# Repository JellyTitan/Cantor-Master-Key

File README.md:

# Cantor Master Key (Formerly 'Cantor MX')
This is a Cantor variant adjusted to support multiple switches, add hot swop kailh V1 & V2 sockets, and add a speaker.
> [!ALERT]
> ALL WORK HAS STOPPED ON THIS REPO. After multiple iterations, I concluded that this is a poor idea and abbandonded the project. The pins on the footprints are all just a little different, so it comes out looking like swiss cheese, and really not working well at all. Ultimately i found that  without three solid points of contact, the switches would be 'jiggly'. The jiggle would require keyplates, and the keyplates added cost & complexity. Reducing cost and complexity was driving this project. 

Version 1.4 **(UNTESTED)** adds:
* breakoff pinky clusters
* Keys 4, 14 & 25 fixed ground zone islands
* Updated switch footprint to prevent ground islands.
* Fixed Choc slot off center by .1 to fix slight skew. (Updated wrapping solder mask.)
* Combined cherry mx and red dragon hole to reduce drilling. 
* Fixed broken speaker footprint.
* ~~todo: Poke-yoke ground zone errors by connecting all gnd pads in footrpint~~

Version 1.3 **(TESTED - Buggy)** (PCB ~~ordered~~ received) currently supports:
* **NOTE TO SELF: In v1.3 Keys 4, 14 & 25 have ground zone islands - these switches will probably not work!!**
* Cherry MX full size 5 pin only. (Aka "[PCB mount](https://deskthority.net/wiki/Switch_mount)")
* [Cherry MX Low profile](https://www.cherrymx.de/en/cherry-mx/mx-low-profile/mx-low-profile-red.html) (Aka "MXLP") 
* [Gateron Low Profile](https://www.gateron.co/products/gateron-low-profile-mechanical-switch-set) (KS-27)
* [Kailh Choc V1](http://www.kailh.com/en/Products/Ks/CS/321.html) (PG1350) - Can use hotswap sockets or be soldered in.
* [Kailh Choc V2](http://www.kailh.com/en/Products/Ks/CS/757.html) (PG1353) - Can use hotswap sockets or be soldered in.
* [TTC KS32](https://deskthority.net/wiki/TTC_KS32_series) (Cherry MX Low Profile Clones)
* RedDragon MX Low profile (No data sheet available - these probably don't work?) 

This version _does not_ support
* Cherry MX full size 3 pin, aka "[Plate mount](https://deskthority.net/wiki/Switch_mount)". (Only 2 good points of contact, so it's too wiggly. Would need a plate).
* [Kailh Notebook "X" Scissor](http://www.kailh.com/en/Products/Ks/NotebookS/649.html) (CPG142501D02) The corner mounting holes conflict with Kailh V2 corner pin. That pin is not electrically relevent, but helps with orientation. Maybe add this in the future?
* Cherry MX [Ultra low profile](https://www.cherrymx.de/en/cherry-mx/mx-ultra-low-profile/mx-ulp-click.html) (Too hard to find).

All of these except the Choc V1s will use MX keycaps. MX keycaps are slightly larger than Choc V1 caps that are used in the original cantor so the layout has been adjusted accordingly. None of the routing has changed, so any Cantor V1.0 firmware will work with the board.

* V1.1 (pcb/gerbers/Cantor_MXv1.1.zip) has been produced with JLCPCB and confirmed to work. This only supports choc v1, choc v2, and MX full size switches. When using full size cherry MX switches, the 5 pin is recommended because the center hole is enlarged to support Kailh Chocs, so the 3 pin full size cherry MX switch will be unstable. It's still workable, but you'll likely have a few tilted keys, or need to create a plate.
* V1.3 Is a work in progress and has not been validated. This version has additonal key support. I threw in a piezo speaker too because, why not?
Improved pin hole dimensions for 3 pin cherry MX stability. Moved TRRS jack to allow for larger thumb cluster keycaps.

Todo:
* Updated the licensing?
* Update schematic for TX/RX TRRS Crossover.
* ~~Should this be updated for the pi2040 (Currently uses blackpill 401).~~ There is already a "Piantor". If this footprint works, make a mash up. 
* On test print 1.3, red was extra, so i went with blue. Try Elecrow next time?
* On test print 1.3, 4-6-23, jlcpcb charged an extra $7.50USD for having an abundance of slots. Try elecrow, or reduce slots. Maybe make the blackpill flippable to reduce by 40 apertures? (Pulling red dragon only reduces by 21 slots, since it shares a ground).

V1.4

V1.3

V1.1

## How to order this board from a PCB vendor.

Helpful info if it's your first time ordering a PCB.

Most PCB vendors have a similar ordering process. I use [JLCPCB](https://jlcpcb.com/) because they are usually the most cost effective. I've had good luck with [Elecrow](https://www.elecrow.com/) too. [You can find PCB price comparison tools online.](https://pcbshopper.com/) When comparing pricing, the board dimensions are 99 x 143mm. (Usually anything under 100x100mm is really cheap - so be sure to use those dimensions when pricing).

The production files are known as "gerbers", and they are usually uploaded as a `.zip` file. (It's essentially a collection of files for each layer of the board, like holes, graphics, traces etc.) In this repo, the file is at `cantor-choc-V2/pcb/Gerbers_ChocV2/Cantor_Choc_V2.zip`. (File & path name may change during development)

@todo - revise path before pull request.

The homepage of JLCPCB has a drag & drop upload. Drag the gerber `.zip` and drop it on the "add gerber file" box.

While the file is uploading, it will take you to an options screen. Once the board size is detected<sup>1</sup>, the price<sup>3</sup> will update accordingly.
Changing the pcb color<sup>2</sup> may impact production time and price.
Shipping estimates<sup>4</sup> can vary widely, so be sure to check those. (You'll see these options again during checkout).

It's worth noting, the default pcb surface finish contains Lead. For boards in cases, this is usually not a problem. If you're going to rock a naked board, consider going with "lead free" for a few bucks more.

`@todo - Site sources?`

The remainder of the checkout process is standard ecommerce stuff. After you pay for your order, it will be reviewed before going into production. They will let you know if the file has any issues.

# Cantor Keyboard
The Cantor keyboard is a 42 key diodeless split keyboard, designed with simplicity in mind. It is inspired on the popular [corne](https://github.com/foostan/crkbd), [ferris](https://github.com/pierrechevalier83/ferris) and [sweep](https://github.com/davidphilipbarr/Sweep) keyboards, aiming to provide a more ergonomic (stronger column stagger) corne-like layout with a simple, easy to assemble and cheap design.

The keyboard uses choc switches with choc spacing. Therefore, only MBK keycaps can be used.

### Why diodeless?

A diodeless design reduces the keyboard assembly time, as the amount of components to solder is significantly reduced.
Moreover, soldering diodes can cause trouble during the keyboard build. Diodes need to be placed in the correct direction, if not, the keys won't work well!
Eliminating diodes will prevent many errors during the assembly process.

## Disclaimers

All the designs and files are provided "AS IS" without any warranty or support.

## Design philosophy

The Cantor is designed with the following goals:

- Comfort
- Powerful
- Low cost
- Simplicity
- Ease of build
- USB-C
- No diodes

The PCB is reversible to reduce manufacturing costs.

## Getting started

Would you like to build this keyboard? Then continue reading!

You can also buy a kit to build the Cantor keyboard from one of the **honorable sponsors**:

<br><br><br><br>

### Bill of Materials

To build the keyboard, you will need the following materials:

- 2x PCB boards (both are equal since they are reversible)
- 2x STM32F401CC blackpill microcontrollers (they are cheap on aliexpress)
- Pins and sockets for the microcontrollers (blackpill needs 20 pin stripes)
- 42 Choc v1 switches
- 42 MBK keycaps
- Some little rubber feet/bumpers (recommended 6 mm of diameter)
- 2x TRRS jacks (PJ-320A)
- 1x TRRS cable
- 1x USB cable compatible with your computer and the blackpill

### Order the PCB

Download the gerber file from realeses, and submit it to your favorite PCB manufacturer. The keyboard designs have been tested with JLCPCB.

Note: if you don't want a random tracking number to be printed in the PCB, make sure to select the option 'Remove Order Number' in JLCPCB.

### How to Build

To build the keyboard, you'll also need a soldering iron and some tin. Follow the [build guide](doc/build_guide.md).

### Firmware

The Cantor keyboard uses the QMK firmware. Firmware for this keyboard is coming soon to the main QMK repository with [this PR](https://github.com/qmk/qmk_firmware/pull/16552).

To flash the firmware to the microcontroller connect the blackpill to your computer and set it to bootloader mode. To do this the first time:

1. Press and hold the BOOT0 button.
2. Press and release the NRST button.
3. Release the BOOT0 button.

The following times you want to flash the keyboard, it is much simpler thanks to bootmagic. Hold the top left key of the keyboard and plug the microcontroller. If flashing the right part, hold the top right key.

## Feedback

If you have build this keyboard, please fill [this form](https://forms.gle/nfJCsei5hyHbjaHn9) to provide feedback. This will help to improve the keyboard design in future revisions.

Also, you can open an issue reporting any problem or feature request.

## Support

The development of a keyboard takes time and money. If you like this keyboard a want to support me for the work and to develop future revisions of the keyboard, consider donating:

PayPal: 
GitHub: [Here](https://github.com/sponsors/diepala)

### Honorable sponsors

Thank you very much to everyone contributing and/or sonponsoring this project. Special thanks to the honorable sponsors:

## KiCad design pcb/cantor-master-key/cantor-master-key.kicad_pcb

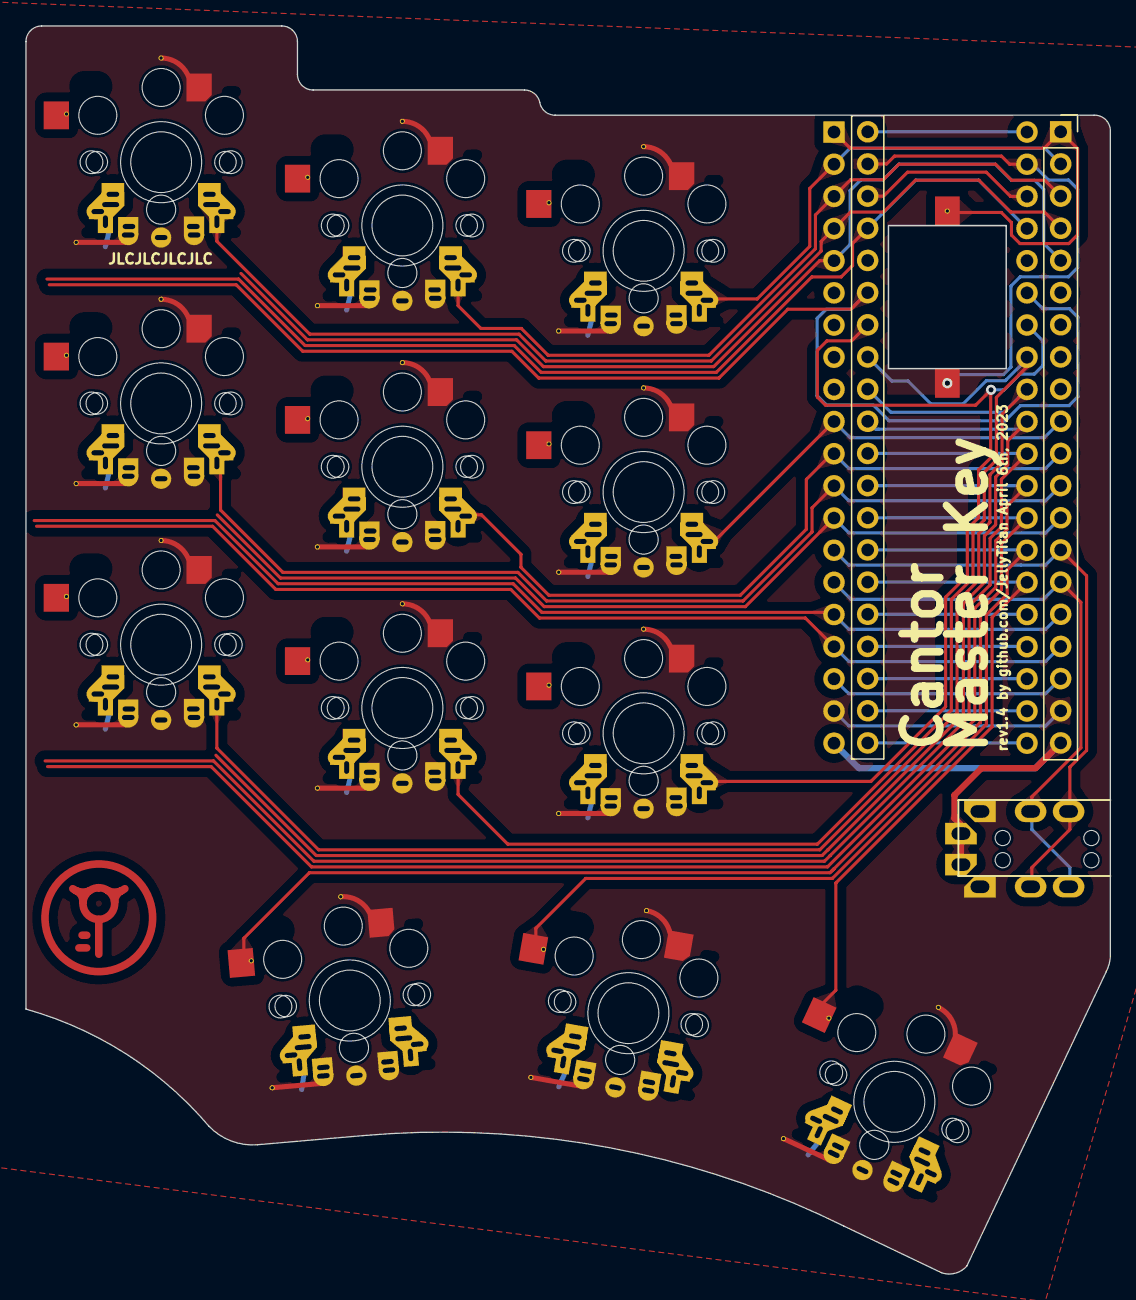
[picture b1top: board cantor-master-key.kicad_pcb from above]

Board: 2 copper layers, 85.6 x 98.6 mm, 15 parts (0 on the bottom side), 17 nets.

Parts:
J1: TRRS; MJ-4PP-9_CANTOR_KITCHEN_SINK
K03, K04, K05, K13, K14, K15, K23, K24, K25, K30, K31, K32: KEYSW; ALL LOWs CANTOR v4.1
LS1: AST1109MLTRQ_MAL; AST1109MLTRQ
U1: YAAJ_WeAct_BlackPill_Part_Like; Cantor_DS_YAAJ_WeAct_BlackPill_2

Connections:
+3V3: J1.1 (SLEEVE), U1.20 (3V3), U1.38 (3V3)
/RX: J1.3 (RING1), U1.15 (PB7)
/TX: J1.4 (RING2), U1.14 (PB6)
/k03: K03.1, U1.4 (PB15)
/k04: K04.1, U1.3 (PB14)
/k05: K05.1, U1.2 (PB13)
/k13: K13.1, U1.12 (PB4)
/k14: K14.1, U1.11 (PB3)
/k15: K15.1, U1.10 (PA15)
/k23: K23.1, U1.32 (PA6)
/k24: K24.1, U1.33 (PA7)
/k25: K25.1, U1.34 (PB0)
/k30: K30.1, U1.28 (PA2)
/k31: K31.1, U1.27 (PA1)
/k32: K32.1, U1.26 (PA0)
AUDIO: LS1.1, U1.1 (PB12)
GND: J1.2 (TIP), K03.2, K04.2, K05.2, K13.2, K14.2, K15.2, K23.2, K24.2, K25.2, K30.2, K31.2, K32.2, LS1.2, U1.19 (GND), U1.39 (GND)

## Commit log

2023-05-01 First commit after splitting from Cantor MX
2023-05-01 Doc and library migration from Cantor MX
2023-05-01 Fixed library routing
2023-05-01 Made truncated version for footprint prototype
2024-01-06 Update README.md
    Note about abandonment

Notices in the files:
parts and their libraries:
Copyright 2021 Accelerated Designs. All rights reserved.
